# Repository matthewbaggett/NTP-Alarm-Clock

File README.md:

# NTP-Alarm-Clock

## Components

 * ESP8266 Microcontroller
 * [Pushswitches](http://cpc.farnell.com/kitronik/4677/push-button-arcade-style-blue/dp/SW05324?MER=sy-me-pd-mi-acce)
 * [i2c 4 digit 7 segment display](http://www.ebay.co.uk/itm/New-Red-1-2-4-Digit-7-Seven-Segment-LED-Display-IIC-for-Arduino-/252530211008?hash=item3acbf938c0)

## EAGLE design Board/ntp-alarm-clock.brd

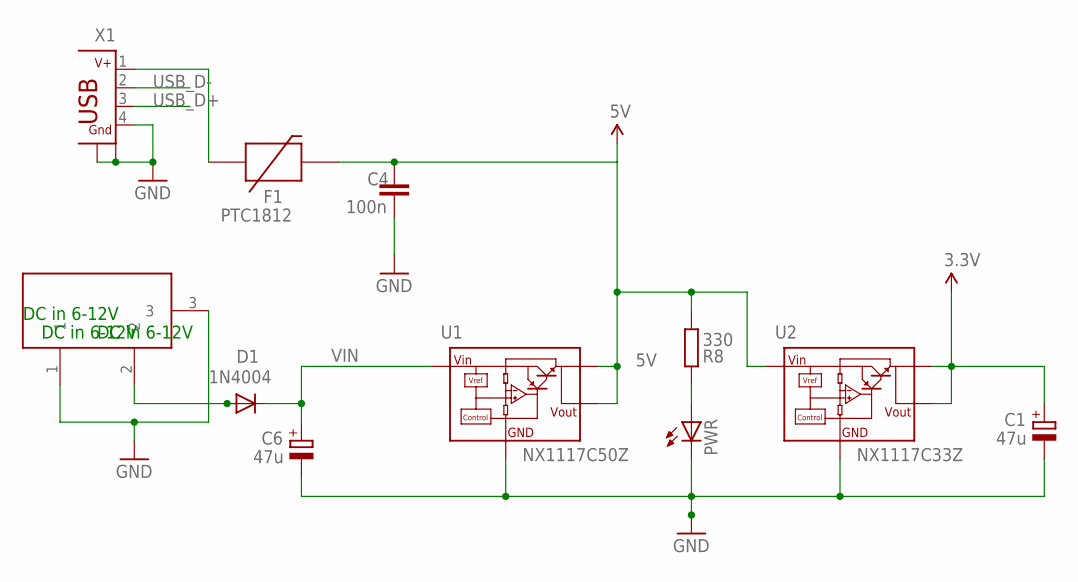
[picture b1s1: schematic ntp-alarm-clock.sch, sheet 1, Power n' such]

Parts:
C1, C6: 47u; PANASONIC_D
C4: 100n; C1206
D1: 1N4004; SMA-DIODE
DC1: 9V in; DC-21MM
F1: PTC1812; C1812
PWR: LED-LCC1206; LCC1206
R8: 330; R1206
U1: NX1117C50Z; SOT223
U2: NX1117C33Z; SOT223
X1: CON-USB-B; USB-WSHIELDPADS

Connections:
3.3V: C1.+, U2.2 (VOUT1), U2.4 (VOUT); also elsewhere on the board
5V: C4.2, F1.2, R8.1, U1.2 (VOUT1), U1.4 (VOUT), U2.3 (VIN)
GND: C1.-, C4.1, C6.-, DC1.1, DC1.3, PWR.C, U1.1 (GND), U2.1 (GND), X1.4, X1.SH1 (GND), X1.SH2 (GND); also elsewhere on the board
unnamed: PWR.A, R8.2
unnamed: D1.A, DC1.2
USBV+: F1.1, X1.1
USB_D+: X1.3; also elsewhere on the board
USB_D-: X1.2; also elsewhere on the board
VIN: C6.+, D1.C, U1.3 (VIN)

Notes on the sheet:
DC in 6-12V

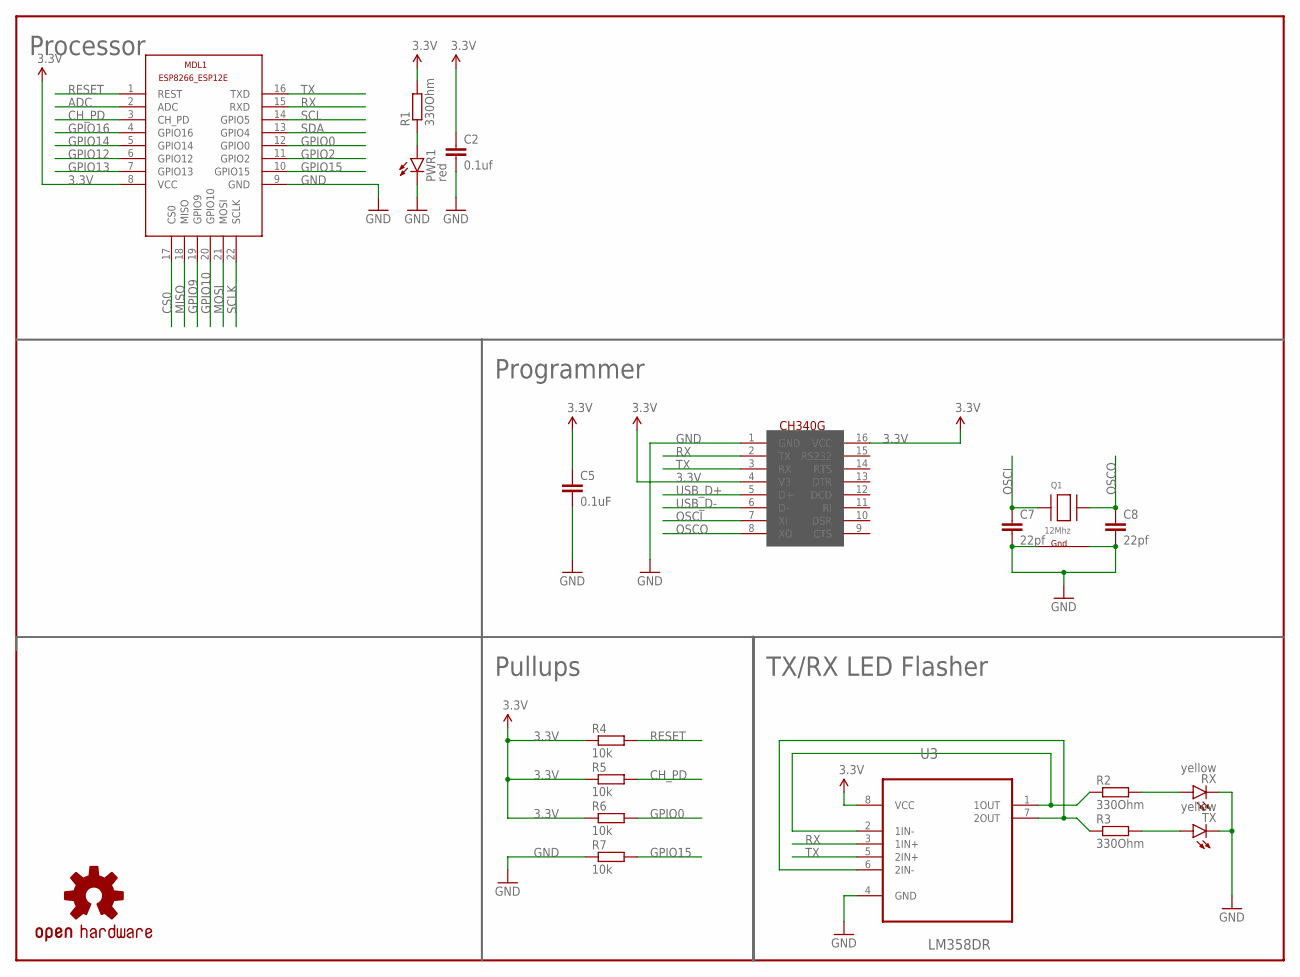
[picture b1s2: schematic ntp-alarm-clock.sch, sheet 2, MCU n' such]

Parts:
C2: 0.1uf; C0805
C5: 0.1uF; C0805
C7, C8: 22pf; C0805
FRAME1: FRAME-LETTERNO_PACKAGE; DUMMY
LOGO1: OSHW-LOGOS; OSHW-LOGO-S
MDL1: ESP8266-12EESP8266-ESP12E; ESP8266-ESP12E
PWR1: red; LED-0603
Q1: 12Mhz; NX3225
R1, R2, R3: 330Ohm; R0805
R4, R5, R6, R7: 10k; R0805
RX: yellow; LED-0603
TX: yellow; LED-0603
U3: LM358DR; SOIC127P600X175-8N
U$2: CH340G; SOIC16

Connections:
3.3V: C2.1, C5.1, MDL1.8 (VCC), R1.2, R4.1, R5.1, R6.1, U3.8 (VCC), U$2.4 (V3), U$2.16 (VCC); also elsewhere on the board
ADC: MDL1.2 (ADC)
CH_PD: MDL1.3 (CH_PD), R5.2
CS0: MDL1.17 (CS0)
GND: C2.2, C5.2, C7.2, C8.2, MDL1.9 (GND), PWR1.C, Q1.2 (G2), Q1.4 (G1), R7.1, RX.C, TX.C, U3.4 (GND), U$2.1 (GND); also elsewhere on the board
GPIO0: MDL1.12 (GPIO0), R6.2
GPIO2: MDL1.11 (GPIO2)
GPIO9: MDL1.19 (GPIO9)
GPIO10: MDL1.20 (GPIO10)
GPIO12: MDL1.6 (GPIO12)
GPIO13: MDL1.7 (GPIO13)
GPIO14: MDL1.5 (GPIO14)
GPIO15: MDL1.10 (GPIO15), R7.2
GPIO16: MDL1.4 (GPIO16)
MISO: MDL1.18 (MISO)
MOSI: MDL1.21 (MOSI)
unnamed: PWR1.A, R1.1
unnamed: R2.1, U3.1 (1OUT), U3.2 (1IN-)
unnamed: R3.1, U3.6 (2IN-), U3.7 (2OUT)
unnamed: R3.2, TX.A
unnamed: R2.2, RX.A
OSCI: C7.1, Q1.1 (X1), U$2.7 (XI)
OSCO: C8.1, Q1.3 (X2), U$2.8 (XO)
RESET: MDL1.1 (REST), R4.2
RX: MDL1.15 (RXD), U3.3 (1IN+), U$2.2 (TX)
SCL: MDL1.14 (GPIO5)
SCLK: MDL1.22 (SCLK)
SDA: MDL1.13 (GPIO4)
TX: MDL1.16 (TXD), U3.5 (2IN+), U$2.3 (RX)
USB_D+: U$2.5 (D+); also elsewhere on the board
USB_D-: U$2.6 (D-); also elsewhere on the board

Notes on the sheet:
Programmer
Processor
Pullups
TX/RX LED Flasher

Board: 2 copper layers, 31 parts (0 on the bottom side), 22 nets, no tracks yet.

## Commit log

2016-11-22 Box parts
2016-11-22 move to enclosure folder
2016-11-22 Add components list
2016-11-24 Corrections
2016-11-24 Initial board + Schematic

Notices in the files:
parts and their libraries:
SparkFun-Aesthetics: Licensing: Creative Commons ShareAlike 4.0 International - https://creativecommons.org/licenses/by-sa/4.0
SparkFun: Licensing: CC v3.0 Share-Alike You are welcome to use this library for commercial purposes.
SparkFun-Aesthetics: https://creativecommons.org/licenses/by-sa/4.0
